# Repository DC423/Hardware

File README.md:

# Hardware

Hardware design and code are housed here.

2018-08 - [2018 DC423 Hardware Badge](https://github.com/DC423/Hardware/blob/master/DC423-2018-Tracer/README.md)

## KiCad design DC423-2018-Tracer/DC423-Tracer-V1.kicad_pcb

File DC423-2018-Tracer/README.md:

# 2018 DC423 Tracer Badge

## Design
This was my first forway into hardware design and prototyping. I am sure that there are better ways to go about what I did in both the design as well as the programming. You are free to copy the repo and make one yourself. As noted on the silkscreen of the board, I made heavy use of [Charlieplexing](https://en.wikipedia.org/wiki/Charlieplexing) in order to drive the 25 leds with just 6  input/output pins. Once you start playing with the design, you'll find an interesting pattern emerge in the trace layout. At any rate, don't judge too hard on this one...it was the first thing I designed in KiCAD.

## Parts
1  - [ATTINY841-SSU](https://www.mouser.com/ProductDetail/Microchip-Technology-Atmel/ATTINY841-SSU?qs=HVbQlW5zcXVaBIh573n%252bhw%3D%3D)
25 - [1206 Red LEDs](https://www.mouser.com/ProductDetail/Wurth-Electronics/156120RS75000?qs=sGAEpiMZZMseGfSY3csMkWdJa7STmGtdb4K4pupKBd%2fd7%252barQY0%252bPQ%3d%3d)
6  - [1206 100ohm Resistors](https://www.mouser.com/ProductDetail/ROHM-Semiconductor/ESR18EZPJ101?qs=sGAEpiMZZMu61qfTUdNhG1IKPAnaLGejQqWTplBhA2M%3d)
1  - [CR2032 Battery Holder](https://www.mouser.com/ProductDetail/Linx-Technologies/BAT-HLD-001?qs=sGAEpiMZZMtT9MhkajLHrnz%2fFPUZSgO1koSsSyYdFD4%3d)

The initial design used a different [CR2032 holder](https://www.mouser.com/ProductDetail/Keystone-Electronics/1058?qs=1Og3oR3ILyCdlFdchHwycQ%3D%3D) but that was too much of a pain to remove the battery since there is no switch to turn the badge on and off.

## Notes
This was also the first time I did any SMD soldering work. I had a hot air rework station that made the job super easy. The boards were ordered from [OSHPark](https://oshpark.com/) and the solder paste stencil was ordered from [OSHStencils](https://www.oshstencils.com/). The ICSP programmer was made using a how-to I found on [Instructables](https://www.instructables.com/id/Pogo-Pin-Programming-Connector/). There are a bunch of tutorials on how to turn an Arduino into a programmer so I won't list it on here.

## Programming
The code for this was initially made on [Tinkercad](https://www.tinkercad.com/things/gh2c09ekxLf-terrific-sango) then pulled down and programmed into the ATTiny841 after it was put on the board. As a side note, you have to flash a bootloader on there first. Who knew?

## What does it look like?

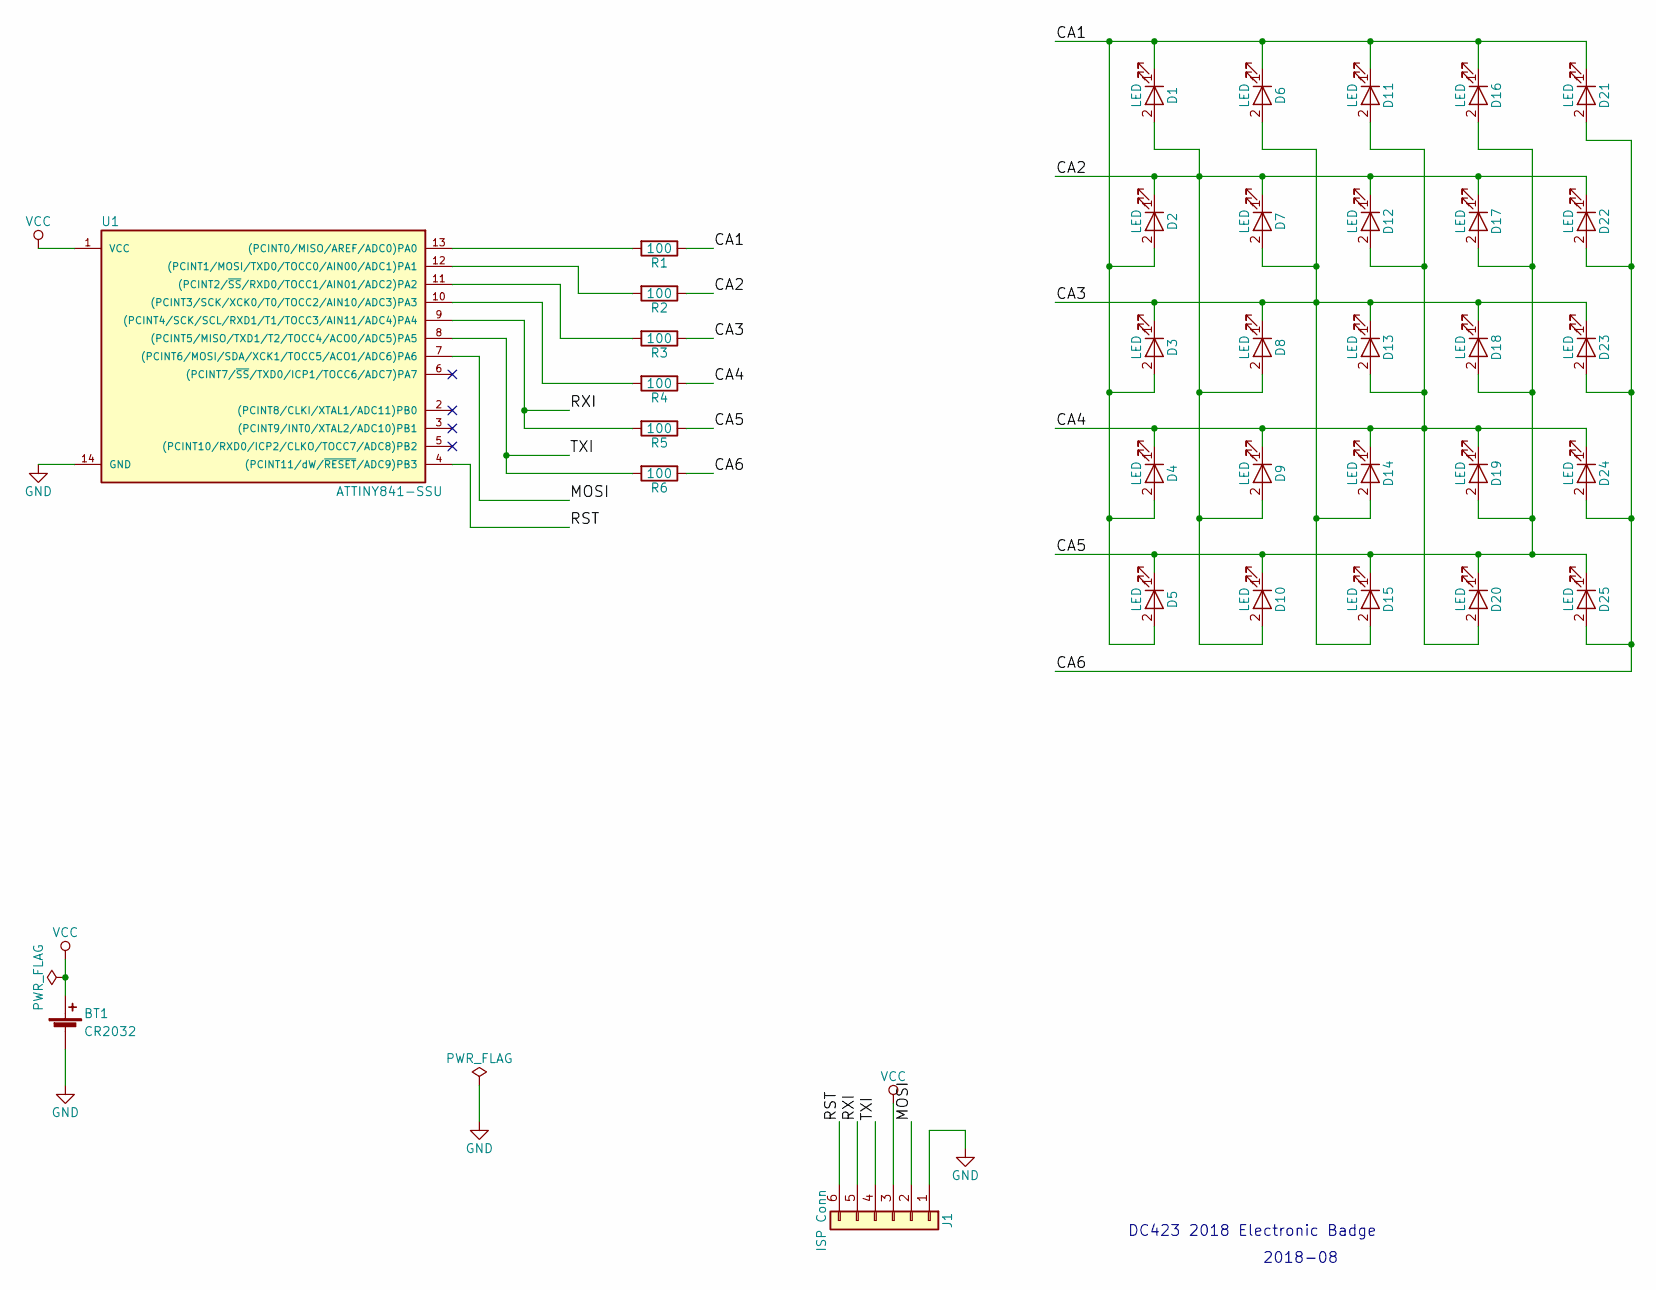
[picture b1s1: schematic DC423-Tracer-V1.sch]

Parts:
BT1: CR2032; linx-bat-hld-001
D1, D2, D3, D4, D5, D6, D7, D8, D9, D10, D11, D12, D13, D14, D15, D16, D17, D18, D19, D20, D21, D22, D23, D24, D25: LED; LED_1206
J1: ISP Conn; Pin_Header_Straight_1x06_Pitch2.54mm
R1, R2, R3, R4, R5, R6: 100; R_1206
U1: ATTINY841-SSU; SOIC-14_3.9x8.7mm_Pitch1.27mm

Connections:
/CA1: D1.1 (K), D2.2 (A), D3.2 (A), D4.2 (A), D5.2 (A), D6.1 (K), D11.1 (K), D16.1 (K), D21.1 (K), R1.1
/CA2: D1.2 (A), D2.1 (K), D7.1 (K), D8.2 (A), D9.2 (A), D10.2 (A), D12.1 (K), D17.1 (K), D22.1 (K), R2.1
/CA3: D3.1 (K), D6.2 (A), D7.2 (A), D8.1 (K), D13.1 (K), D14.2 (A), D15.2 (A), D18.1 (K), D23.1 (K), R3.1
/CA4: D4.1 (K), D9.1 (K), D11.2 (A), D12.2 (A), D13.2 (A), D14.1 (K), D19.1 (K), D20.2 (A), D24.1 (K), R4.1
/CA5: D5.1 (K), D10.1 (K), D15.1 (K), D16.2 (A), D17.2 (A), D18.2 (A), D19.2 (A), D20.1 (K), D25.1 (K), R5.1
/CA6: D21.2 (A), D22.2 (A), D23.2 (A), D24.2 (A), D25.2 (A), R6.1
/MOSI: J1.2, U1.7 ((PCINT6/MOSI/SDA/XCK1/TOCC5/ACO1/ADC6)P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)
/RST: J1.6, U1.4 ((PCINT11/dW/~RESET~/ADC9)PB3)
/RXI: J1.5, R5.2, U1.9 ((PCINT4/SCK/SCL/RXD1/T1/TOCC3/AIN11/ADC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)
/TXI: J1.4, R6.2, U1.8 ((PCINT5/MISO/TXD1/T2/TOCC4/ACO0/ADC5)PA5)
GND: BT1.2 (-), J1.1, U1.14 (GND)
unnamed: R1.2, U1.13 ((PCINT0/MISO/AREF/ADC0)PA0)
unnamed: R2.2, U1.12 ((PCINT1/MOSI/TXD0/TOCC0/AIN00/ADC1)PA1)
unnamed: R3.2, U1.11 ((PCINT2/~SS~/RXD0/TOCC1/AIN01/ADC2)PA2)
unnamed: R4.2, U1.10 ((PCINT3/SCK/XCK0/T0/TOCC2/AIN10/ADC3)PA3)
VCC: BT1.1 (+), J1.3, U1.1 (VCC)

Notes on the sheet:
DC423 2018 Electronic Badge
2018-08

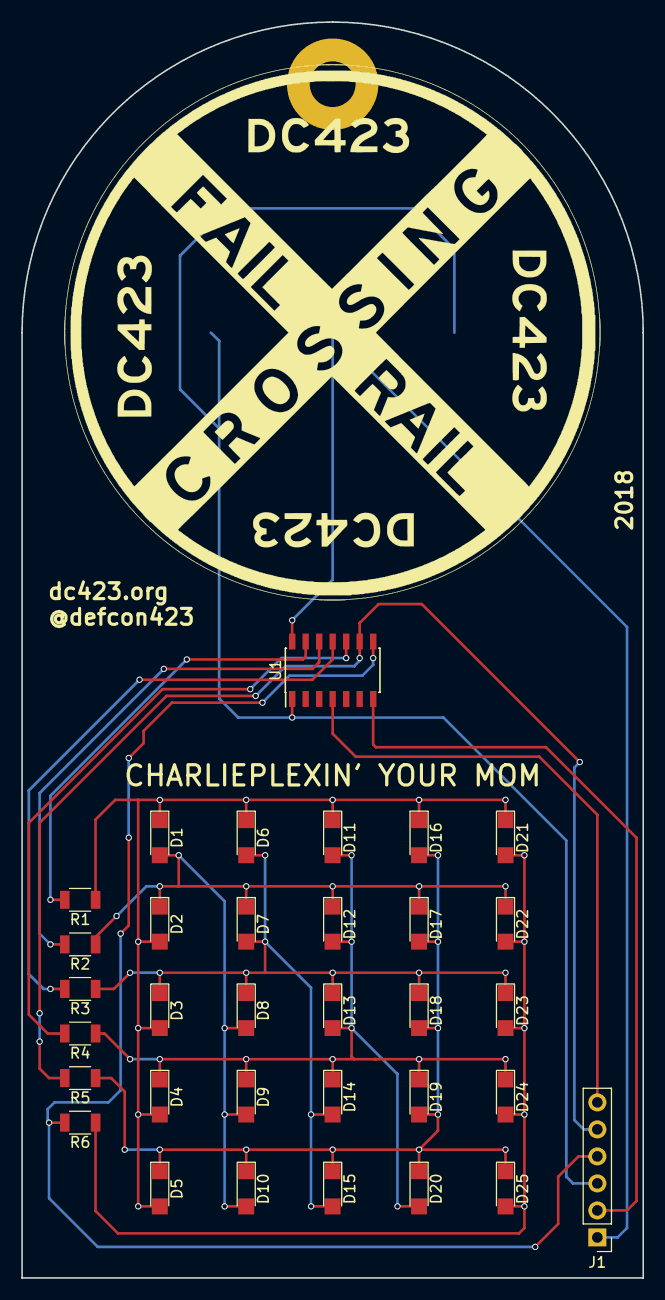
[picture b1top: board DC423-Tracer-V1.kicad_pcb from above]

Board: 2 copper layers, 58.4 x 118.1 mm, 35 parts (1 on the bottom side), 16 nets.

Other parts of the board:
F***: FRail; failrail_2x2

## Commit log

2018-08-05 Initial commit of hardware repo
2018-08-06 Final updates to schematic and added PDF of schematic
2018-08-06 Added codebase and updated README for the badge
2018-09-28 added image of board
